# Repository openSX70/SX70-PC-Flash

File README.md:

# SX70-PC-Flash
This a test PC flash adapter

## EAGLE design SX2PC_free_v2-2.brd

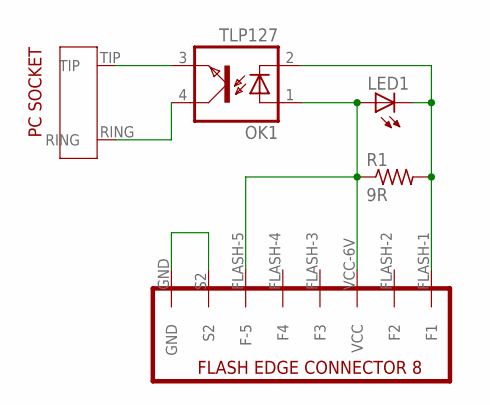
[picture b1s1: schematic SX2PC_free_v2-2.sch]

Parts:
LED1: LEDCHIP-LED0805; CHIP-LED0805
OK1: TLP127; SO-4
R1: 9R; R0603
U$1: SX70-FLASH-EDGE8-MALE; SX70-FLASH-EDGE8
U$2: PC-SOCKET-KAISER-1311

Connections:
GND: LED1.C, OK1.2 (C), R1.2, U$1.FLASH-1 (F1)
unnamed: U$1.GND, U$1.S2
unnamed: LED1.A, OK1.1 (A), R1.1, U$1.FLASH-5 (F-5), U$1.VCC-6V (VCC)
unnamed: OK1.3 (EMIT), U$2.TIP
unnamed: OK1.4 (COL), U$2.RING

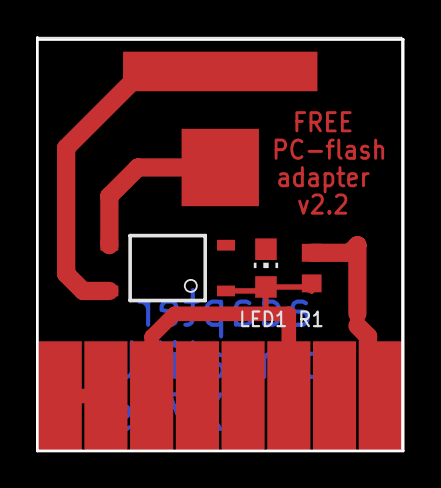
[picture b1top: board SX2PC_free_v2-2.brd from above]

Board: 2 copper layers, 20.3 x 23.0 mm, 5 parts (0 on the bottom side), 5 nets.

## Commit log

2017-11-27 openSX70 test adapter for use of PC flash
    openSX70 test adapter for use of PC flash with the flashbar connector on the SX70 cameras. Not tested.
2017-11-27 Build a prototype and checked operation. Now working. Version 2.0
2017-11-27 Connected F1 and F5 to VCC or it doesn't work!
2018-01-03 Updated to version 2.2
